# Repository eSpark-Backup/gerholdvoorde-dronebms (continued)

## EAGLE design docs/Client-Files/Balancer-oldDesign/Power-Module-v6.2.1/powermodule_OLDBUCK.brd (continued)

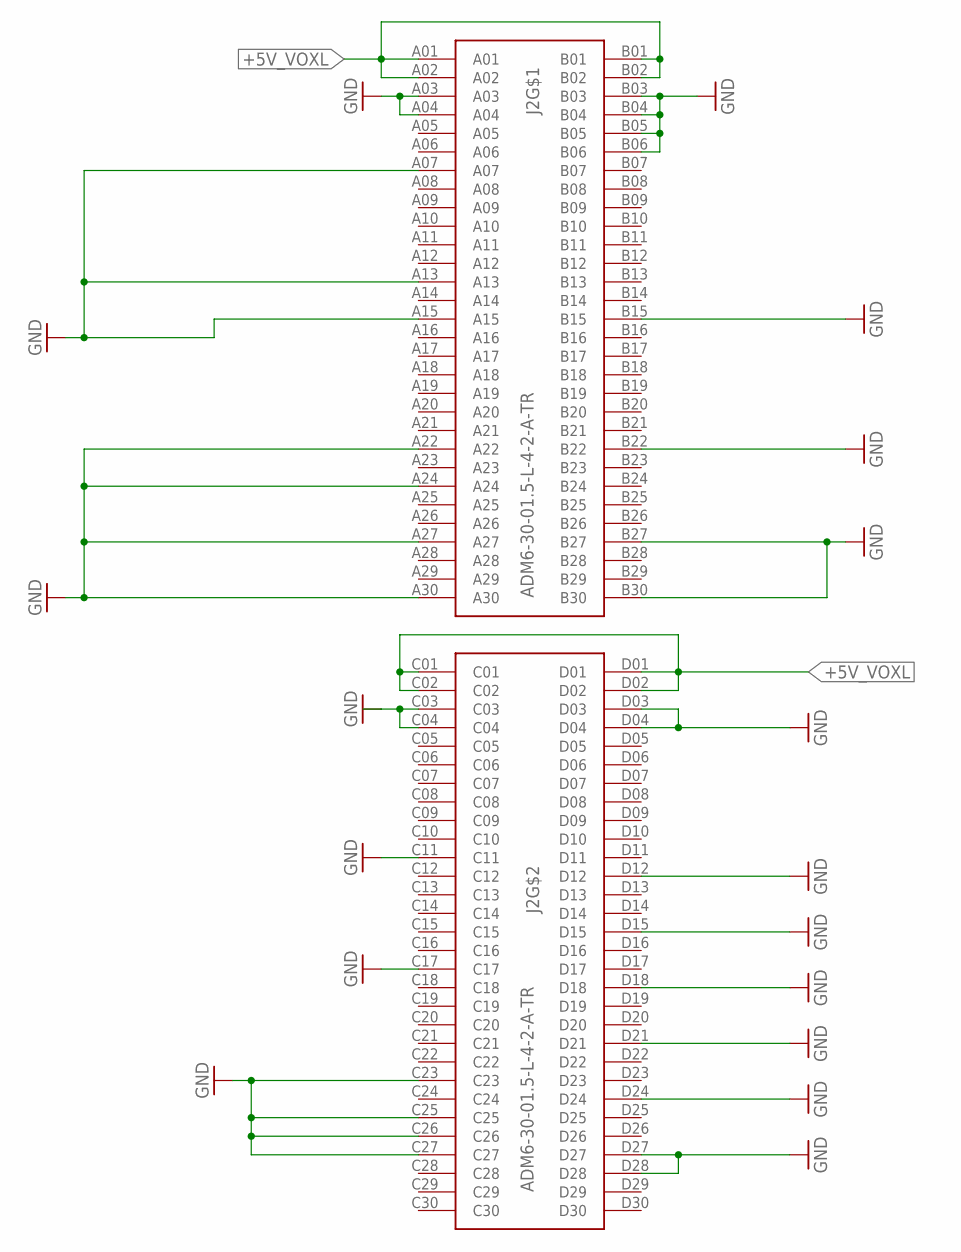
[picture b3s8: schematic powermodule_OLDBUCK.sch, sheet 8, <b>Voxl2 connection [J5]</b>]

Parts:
J2: ADM6-30-01.5-L-4-2-A-TR; SAMTEC_ADM6-30-01.5-L-4-2-A-TR

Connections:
+5V_VOXL: J2.A01, J2.A02, J2.B01, J2.B02, J2.C01, J2.C02, J2.D01, J2.D02; also elsewhere on the board
GND: J2.A03, J2.A04, J2.A07, J2.A13, J2.A15, J2.A22, J2.A24, J2.A27, J2.A30, J2.B03, J2.B04, J2.B05, J2.B06, J2.B15, J2.B22, J2.B27, J2.B30, J2.C03, J2.C04, J2.C11, J2.C17, J2.C23, J2.C25, J2.C26, J2.C27, J2.D03, J2.D04, J2.D12, J2.D15, J2.D18, J2.D21, J2.D24, J2.D27, J2.D28; also elsewhere on the board

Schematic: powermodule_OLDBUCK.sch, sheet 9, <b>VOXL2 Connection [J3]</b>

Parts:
FB: LEDCHIPLED_0805; CHIPLED_0805
J3: QTH-030-01-L-D-ACONN_QTH-030-02-L-D-A-K-FR_S00; CONN_QTH-030-02-L-D-A-K-FR_S00
R11: 1K; R0603
R12: 220?; R0603
U$6: FASTBOOT; EVQ-P7J01P

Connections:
GND: J3.1, J3.10, J3.11, J3.18, J3.21, J3.31, J3.36, J3.44, J3.58, J3.59, R11.2; also elsewhere on the board
GPIO24: R12.2; also elsewhere on the board
unnamed: R11.1, U$6.4
unnamed: FB.C, J3.49, U$6.1
unnamed: FB.A, R12.1
SCL_VOXL: J3.13; also elsewhere on the board
SDA_VOXL: J3.15; also elsewhere on the board
USB-WIFI-DM: J3.12; also elsewhere on the board
USB-WIFI-DP: J3.14; also elsewhere on the board

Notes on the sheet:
Port 9
Note: Deactivate LED when voxl powers on

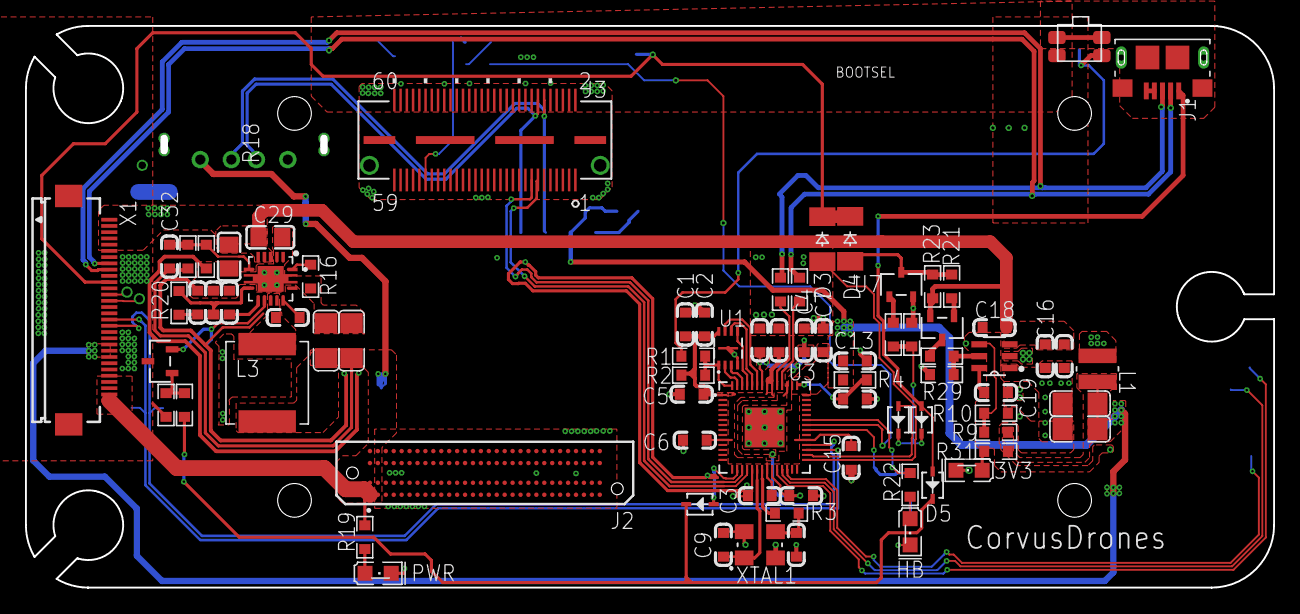
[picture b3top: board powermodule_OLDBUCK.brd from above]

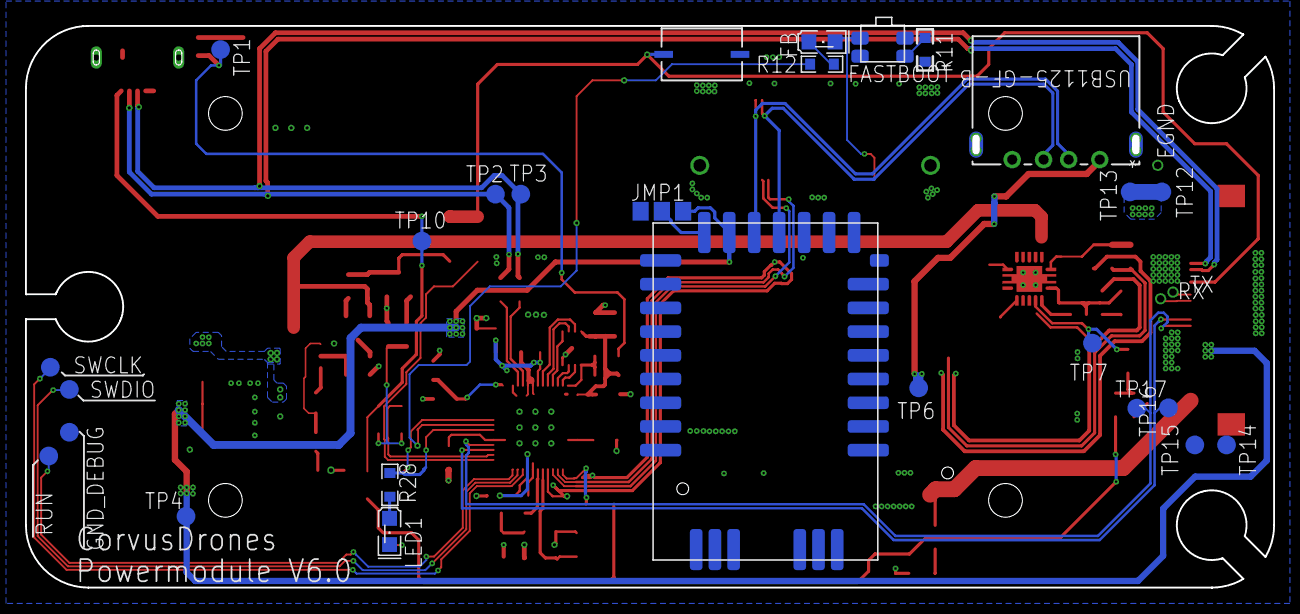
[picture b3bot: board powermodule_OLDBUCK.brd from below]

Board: 2 copper layers, 99.5 x 44.5 mm, 107 parts (30 on the bottom side), 66 nets.

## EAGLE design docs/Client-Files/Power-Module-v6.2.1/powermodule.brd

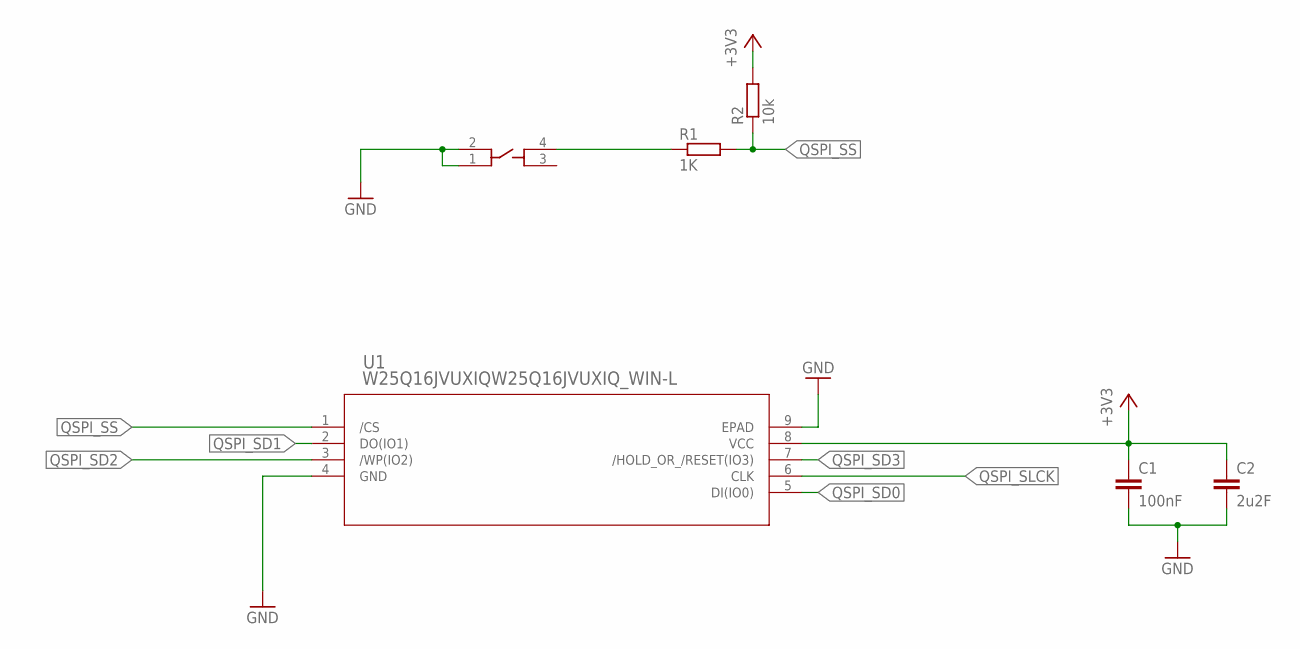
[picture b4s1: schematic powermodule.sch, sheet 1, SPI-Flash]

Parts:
C1: 100nF; C0603
C2: 2u2F; C0603
R1: 1K; R0603
R2: 10k; R0603
SW1: BOOTSEL; EVQ-P7J01P
U1: W25Q16JVUXIQW25Q16JVUXIQ_WIN-L; W25Q16JVUXIQ_WIN-L

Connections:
+3V3: C1.1, C2.1, R2.2, U1.8 (VCC); also elsewhere on the board
GND: C1.2, C2.2, SW1.1, SW1.2, U1.4 (GND), U1.9 (EPAD); also elsewhere on the board
unnamed: R1.1, SW1.4
QSPI_SD0: U1.5 (DI(IO0)); also elsewhere on the board
QSPI_SD1: U1.2 (DO(IO1)); also elsewhere on the board
QSPI_SD2: U1.3 (/WP(IO2)); also elsewhere on the board
QSPI_SD3: U1.7 (/HOLD_OR_/RESET(IO3)); also elsewhere on the board
QSPI_SLCK: U1.6 (CLK); also elsewhere on the board
QSPI_SS: R1.2, R2.1, U1.1 (/CS); also elsewhere on the board

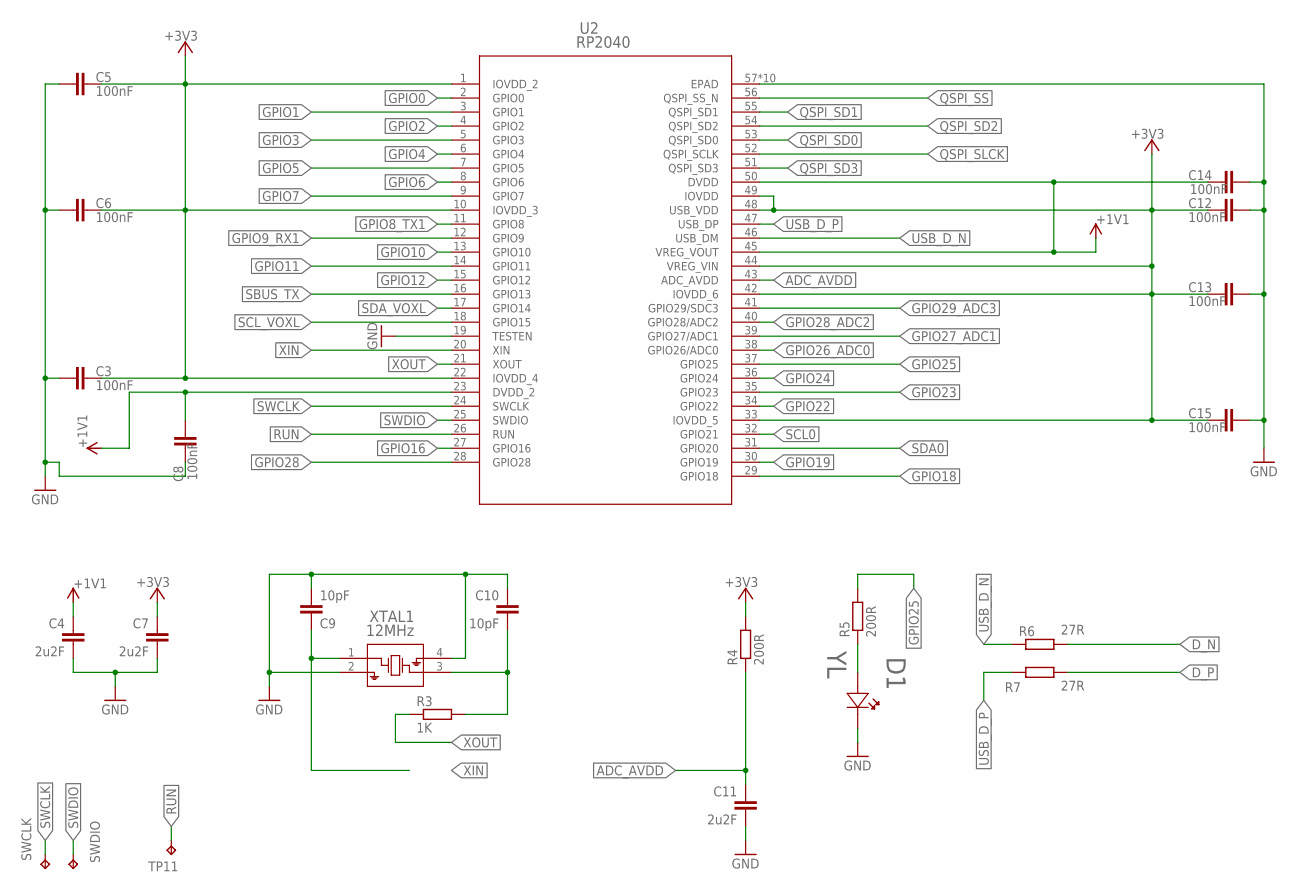
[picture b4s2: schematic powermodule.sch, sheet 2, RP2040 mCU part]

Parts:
C3, C5, C6, C8, C12, C13, C14, C15: 100nF; C0603
C4, C7, C11: 2u2F; C0603
C9, C10: 10pF; C0603
D1: YL; LED_0805
R3: 1K; R0603
R4, R5: 200R; R0603
R6, R7: 27R; R0603
SWCLK: TPTP11R; TP11R
SWDIO: TPTP11R; TP11R
TP11: TPTP11R; TP11R
U2: RP2040; RP2040TR7_RPI-L
XTAL1: 12MHz; SMD3225_3.2X2.5X0.7_MTC-L

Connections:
+1V1: C4.2, C8.1, C14.2, U2.23 (DVDD_2), U2.45 (VREG_VOUT), U2.50 (DVDD)
+3V3: C3.2, C5.1, C6.1, C7.2, C12.1, C13.1, C15.2, R4.2, U2.1 (IOVDD_2), U2.10 (IOVDD_3), U2.22 (IOVDD_4), U2.33 (IOVDD_5), U2.42 (IOVDD_6), U2.44 (VREG_VIN), U2.48 (USB_VDD), U2.49 (IOVDD); also elsewhere on the board
ADC_AVDD: C11.2, R4.1, U2.43 (ADC_AVDD)
D_N: R6.2; also elsewhere on the board
D_P: R7.2; also elsewhere on the board
GND: C3.1, C4.1, C5.2, C6.2, C7.1, C8.2, C9.1, C10.2, C11.1, C12.2, C13.2, C14.1, C15.1, D1.C (1), U2.19 (TESTEN), U2.57 (EPAD), U2.58 (EPAD), U2.59 (EPAD), U2.60 (EPAD), U2.61 (EPAD), U2.62 (EPAD), U2.63 (EPAD), U2.64 (EPAD), U2.65 (EPAD), U2.66 (EPAD), XTAL1.2, XTAL1.4; also elsewhere on the board
GPIO0: U2.2 (GPIO0); also elsewhere on the board
GPIO1: U2.3 (GPIO1); also elsewhere on the board
GPIO2: U2.4 (GPIO2); also elsewhere on the board
GPIO3: U2.5 (GPIO3); also elsewhere on the board
GPIO4: U2.6 (GPIO4); also elsewhere on the board
GPIO5: U2.7 (GPIO5); also elsewhere on the board
GPIO6: U2.8 (GPIO6); also elsewhere on the board
GPIO7: U2.9 (GPIO7); also elsewhere on the board
GPIO8_TX1: U2.11 (GPIO8); also elsewhere on the board
GPIO9_RX1: U2.12 (GPIO9); also elsewhere on the board
GPIO10: U2.13 (GPIO10)
GPIO11: U2.14 (GPIO11)
GPIO12: U2.15 (GPIO12); also elsewhere on the board
GPIO16: U2.27 (GPIO16)
GPIO18: U2.29 (GPIO18)
GPIO19: U2.30 (GPIO19)
GPIO22: U2.34 (GPIO22); also elsewhere on the board
GPIO23: U2.35 (GPIO23); also elsewhere on the board
GPIO24: U2.36 (GPIO24); also elsewhere on the board
GPIO25: R5.2, U2.37 (GPIO25)
GPIO26_ADC0: U2.38 (GPIO26/ADC0); also elsewhere on the board
GPIO27_ADC1: U2.39 (GPIO27/ADC1); also elsewhere on the board
GPIO28: U2.28 (GPIO28); also elsewhere on the board
GPIO28_ADC2: U2.40 (GPIO28/ADC2); also elsewhere on the board
GPIO29_ADC3: U2.41 (GPIO29/SDC3); also elsewhere on the board
unnamed: C10.1, R3.2, XTAL1.3
unnamed: D1.A (2), R5.1
QSPI_SD0: U2.53 (QSPI_SD0); also elsewhere on the board
QSPI_SD1: U2.55 (QSPI_SD1); also elsewhere on the board
QSPI_SD2: U2.54 (QSPI_SD2); also elsewhere on the board
QSPI_SD3: U2.51 (QSPI_SD3); also elsewhere on the board
QSPI_SLCK: U2.52 (QSPI_SCLK); also elsewhere on the board
QSPI_SS: U2.56 (QSPI_SS_N); also elsewhere on the board
RUN: TP11.TP, U2.26 (RUN)
SBUS_TX: U2.16 (GPIO13); also elsewhere on the board
SCL0: U2.32 (GPIO21); also elsewhere on the board
SCL_VOXL: U2.18 (GPIO15); also elsewhere on the board
SDA0: U2.31 (GPIO20); also elsewhere on the board
SDA_VOXL: U2.17 (GPIO14); also elsewhere on the board
SWCLK: SWCLK.TP, U2.24 (SWCLK)
SWDIO: SWDIO.TP, U2.25 (SWDIO)
USB_D_N: R6.1, U2.46 (USB_DM)
USB_D_P: R7.1, U2.47 (USB_DP)
XIN: C9.2, U2.20 (XIN), XTAL1.1
XOUT: R3.1, U2.21 (XOUT)

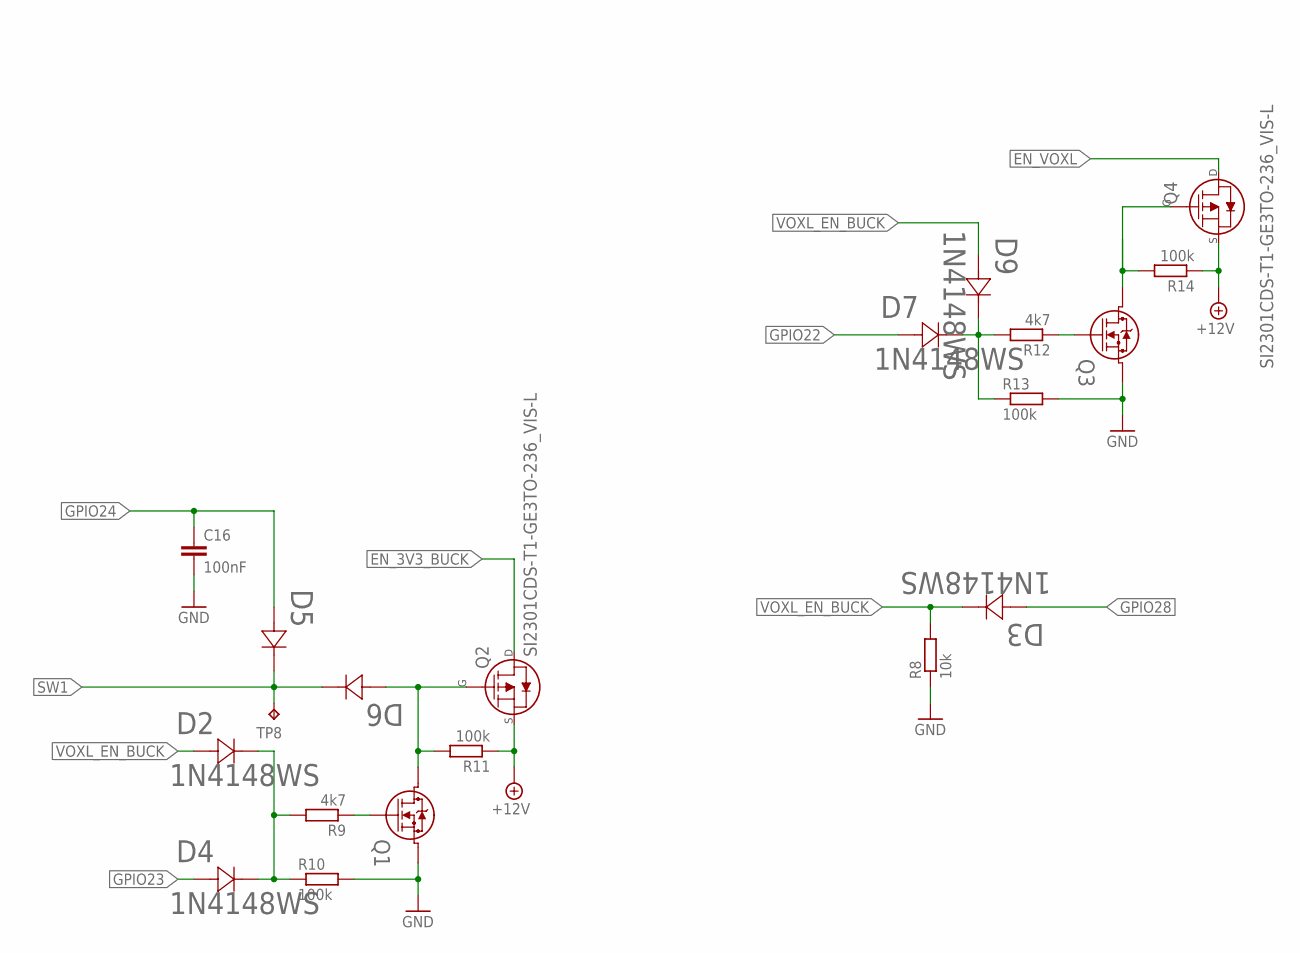
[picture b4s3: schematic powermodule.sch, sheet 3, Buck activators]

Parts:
C16: 100nF; C0603
D2, D3, D4, D7, D9: 1N4148WS; SOD323_NEX-L
D5, D6: MMSD4148T1GSOD-123_ONS-L; SOD-123_ONS-L
Q1, Q3: 2N7002,215TO-236AB_NEX-L; TO-236AB_NEX-L
Q2, Q4: SI2301CDS-T1-GE3TO-236_VIS-L; TO-236_VIS-L
R8: 10k; R0603
R9, R12: 4k7; R0603
R10, R11, R13, R14: 100k; R0603
TP8: TPTP11R; TP11R

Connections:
+12V: Q2.2 (S), Q4.2 (S), R11.1, R14.1; also elsewhere on the board
EN_3V3_BUCK: Q2.3 (D); also elsewhere on the board
EN_VOXL: Q4.3 (D); also elsewhere on the board
GND: C16.2, Q1.2 (3), Q3.2 (3), R8.1, R10.2, R13.2; also elsewhere on the board
GPIO22: D7.2; also elsewhere on the board
GPIO23: D4.2; also elsewhere on the board
GPIO24: C16.1, D5.2; also elsewhere on the board
GPIO28: D3.2; also elsewhere on the board
unnamed: D7.1, D9.1, R12.2, R13.1
unnamed: D6.2, Q1.3 (2), Q2.1 (G), R11.2
unnamed: Q1.1, R9.1
unnamed: Q3.3 (2), Q4.1 (G), R14.2
unnamed: D2.1, D4.1, R9.2, R10.1
unnamed: Q3.1, R12.1
SW1: D5.1, D6.1, TP8.TP; also elsewhere on the board
VOXL_EN_BUCK: D2.2, D3.1, D9.2, R8.2; also elsewhere on the board

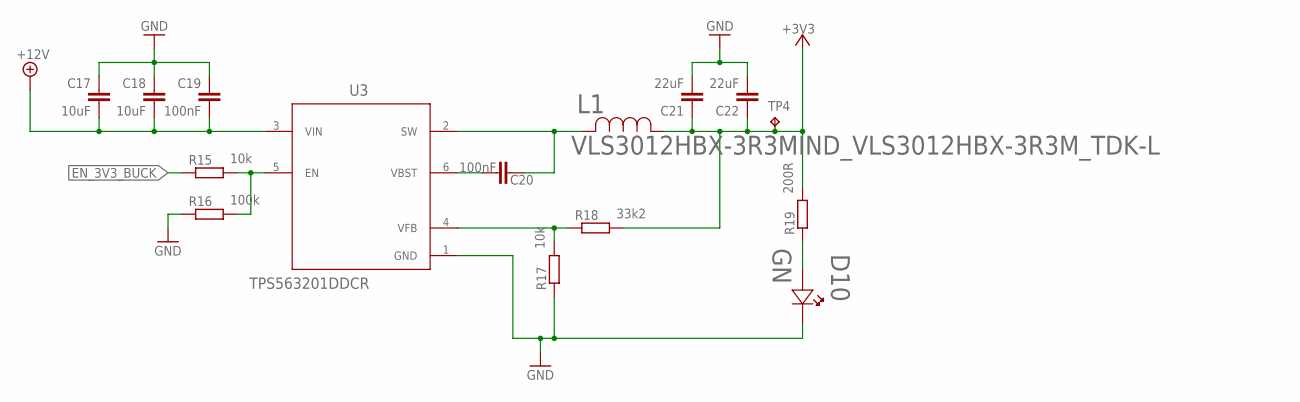
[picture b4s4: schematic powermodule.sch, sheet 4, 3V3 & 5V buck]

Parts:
C17, C18: 10uF; C0603
C19, C20: 100nF; C0603
C21, C22: 22uF; C1206
D10: GN; LED_0805
L1: VLS3012HBX-3R3MIND_VLS3012HBX-3R3M_TDK-L; IND_VLS3012HBX-3R3M_TDK-L
R15, R17: 10k; R0603
R16: 100k; R0603
R18: 33k2; R0603
R19: 200R; R0603
TP4: TPTP11R; TP11R
U3: TPS563201DDCR; DDC0006A_L

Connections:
+3V3: C21.1, C22.1, L1.1, R18.2, R19.2, TP4.TP; also elsewhere on the board
+12V: C17.1, C18.1, C19.1, U3.3 (VIN); also elsewhere on the board
EN_3V3_BUCK: R15.1; also elsewhere on the board
GND: C17.2, C18.2, C19.2, C21.2, C22.2, D10.C (1), R16.1, R17.1, U3.1 (GND); also elsewhere on the board
unnamed: R15.2, R16.2, U3.5 (EN)
unnamed: R17.2, R18.1, U3.4 (VFB)
unnamed: C20.1, U3.6 (VBST)
unnamed: C20.2, L1.2, U3.2 (SW)
unnamed: D10.A (2), R19.1

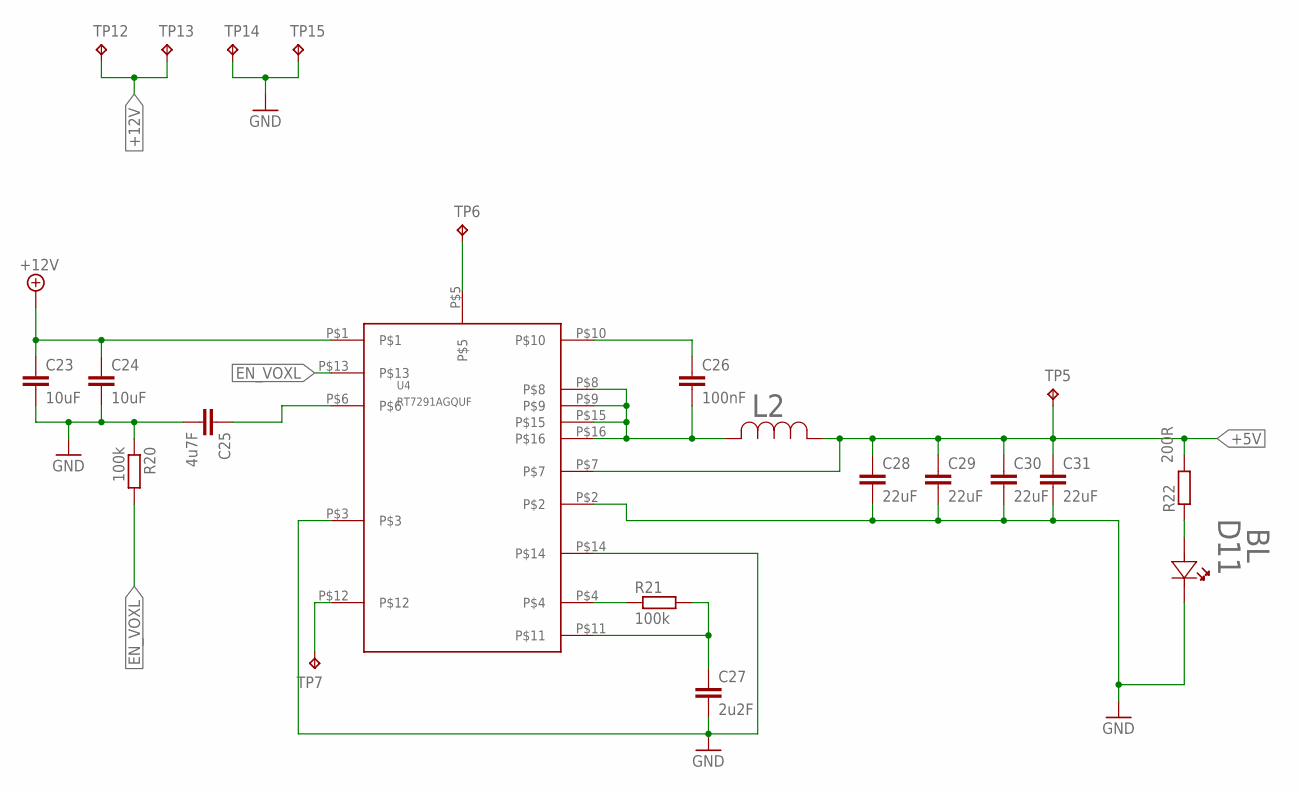
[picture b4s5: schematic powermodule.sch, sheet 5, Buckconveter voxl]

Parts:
C23, C24: 10uF; C0805
C25: 4u7F; C0603
C26: 100nF; C0603
C27: 2u2F; C0603
C28, C29, C30, C31: 22uF; C1206
D11: BL; LED_0805
L2: HA72L-06301R5LFTR
R20, R21: 100k; R0603
R22: 200R; R0603
TP5, TP6, TP7, TP12, TP13, TP14, TP15: TPTP11R; TP11R
U4: RT7291AGQUF

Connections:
+5V: C28.1, C29.1, C30.1, C31.1, L2.P$1 (1), R22.2, TP5.TP, U4.P$7; also elsewhere on the board
+12V: C23.1, C24.1, TP12.TP, TP13.TP, U4.P$1; also elsewhere on the board
EN_VOXL: R20.2, U4.P$13; also elsewhere on the board
GND: C23.2, C24.2, C25.2, C27.2, C28.2, C29.2, C30.2, C31.2, D11.C (1), R20.1, TP14.TP, TP15.TP, U4.P$2, U4.P$3, U4.P$14; also elsewhere on the board
unnamed: C26.2, L2.P$2 (2), U4.P$8, U4.P$9, U4.P$15, U4.P$16
unnamed: C25.1, U4.P$6
unnamed: C27.1, R21.2, U4.P$11
unnamed: TP7.TP, U4.P$12
unnamed: R21.1, U4.P$4
unnamed: D11.A (2), R22.1
unnamed: TP6.TP, U4.P$5
unnamed: C26.1, U4.P$10

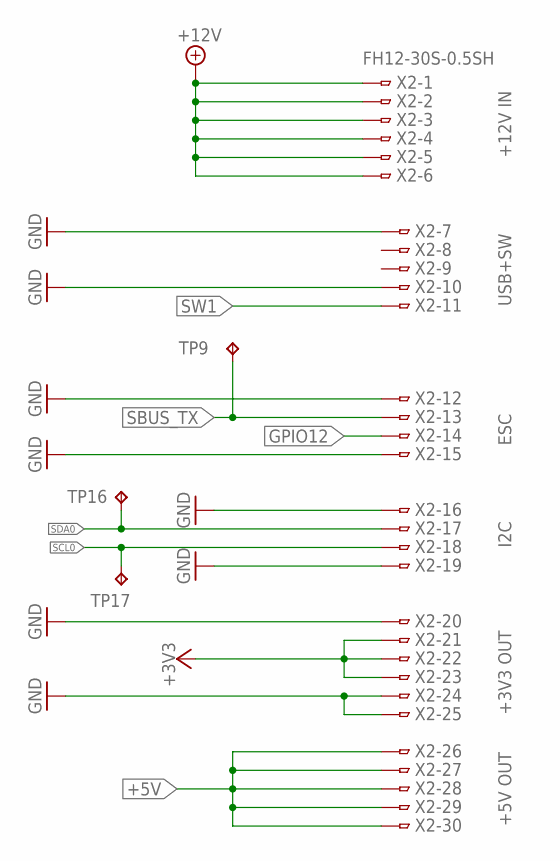
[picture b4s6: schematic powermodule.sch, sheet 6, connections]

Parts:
TP9, TP16, TP17: TPTP11R; TP11R
X2: FH12-30S-0.5SH

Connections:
+3V3: X2.21, X2.22, X2.23; also elsewhere on the board
+5V: X2.26, X2.27, X2.28, X2.29, X2.30; also elsewhere on the board
+12V: X2.1, X2.2, X2.3, X2.4, X2.5, X2.6; also elsewhere on the board
GND: X2.7, X2.10, X2.12, X2.15, X2.16, X2.19, X2.20, X2.24, X2.25; also elsewhere on the board
GPIO12: X2.14; also elsewhere on the board
SBUS_TX: TP9.TP, X2.13; also elsewhere on the board
SCL0: TP17.TP, X2.18; also elsewhere on the board
SDA0: TP16.TP, X2.17; also elsewhere on the board
SW1: X2.11; also elsewhere on the board

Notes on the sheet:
+5V OUT
+3V3 OUT
I2C
ESC
USB+SW
+12V IN

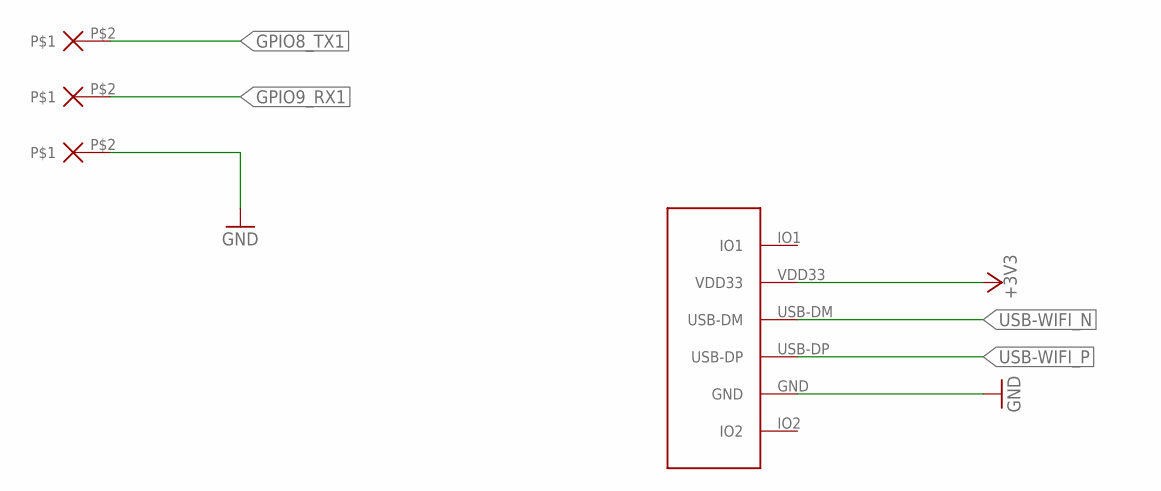
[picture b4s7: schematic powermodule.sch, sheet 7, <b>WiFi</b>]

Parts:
GND_SER: TH-0.75/0.6
W1: WIFI-RTL8188EUS
X3, X4: TH-0.75/0.6

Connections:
+3V3: W1.VDD33; also elsewhere on the board
GND: GND_SER.P$2, W1.GND; also elsewhere on the board
GPIO8_TX1: X3.P$2; also elsewhere on the board
GPIO9_RX1: X4.P$2; also elsewhere on the board
USB-WIFI_N: W1.USB-DM; also elsewhere on the board
USB-WIFI_P: W1.USB-DP; also elsewhere on the board

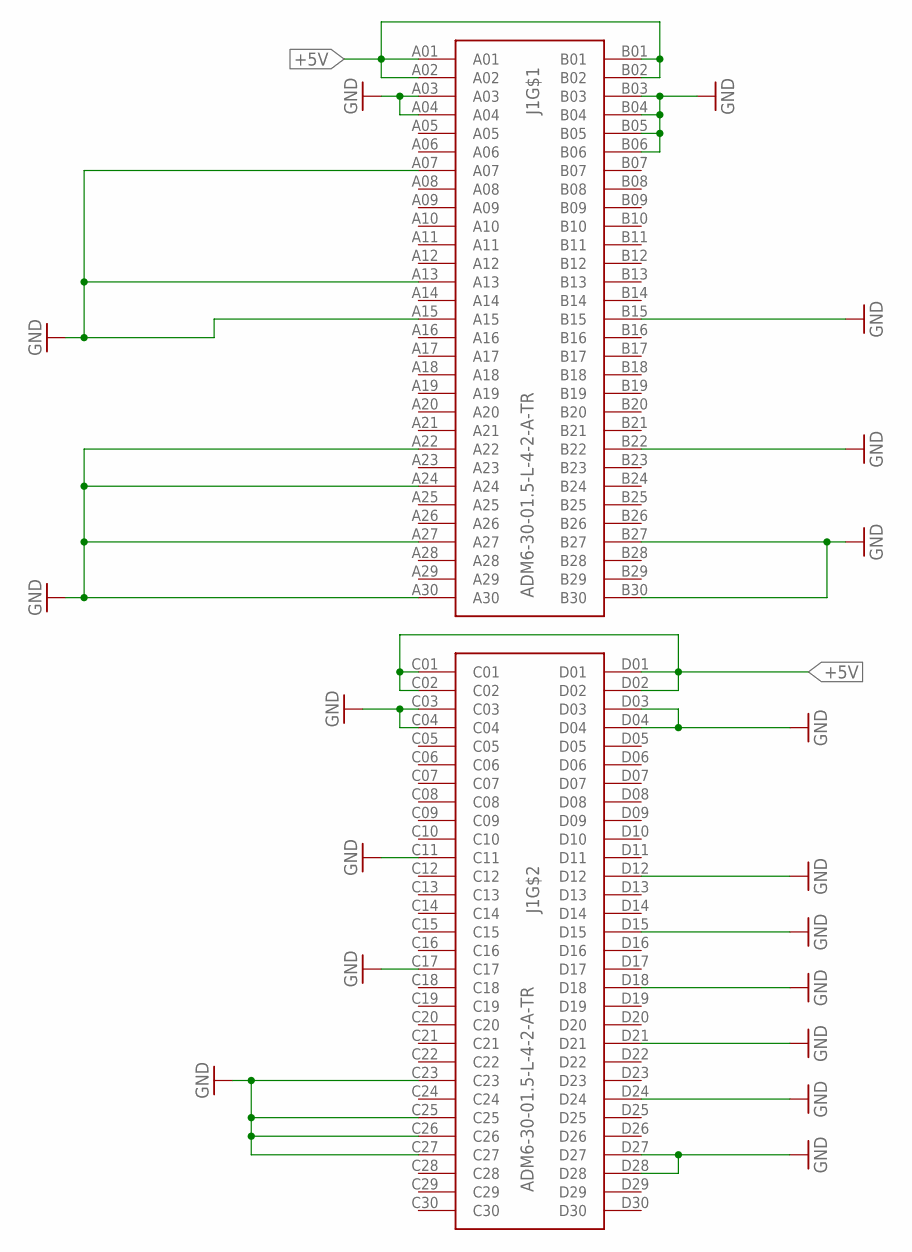
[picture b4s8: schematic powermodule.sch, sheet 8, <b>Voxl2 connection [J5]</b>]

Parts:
J1: ADM6-30-01.5-L-4-2-A-TR; SAMTEC_ADM6-30-01.5-L-4-2-A-TR

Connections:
+5V: J1.A01, J1.A02, J1.B01, J1.B02, J1.C01, J1.C02, J1.D01, J1.D02; also elsewhere on the board
GND: J1.A03, J1.A04, J1.A07, J1.A13, J1.A15, J1.A22, J1.A24, J1.A27, J1.A30, J1.B03, J1.B04, J1.B05, J1.B06, J1.B15, J1.B22, J1.B27, J1.B30, J1.C03, J1.C04, J1.C11, J1.C17, J1.C23, J1.C25, J1.C26, J1.C27, J1.D03, J1.D04, J1.D12, J1.D15, J1.D18, J1.D21, J1.D24, J1.D27, J1.D28; also elsewhere on the board

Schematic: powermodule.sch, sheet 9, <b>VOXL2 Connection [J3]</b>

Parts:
D12: YL; LED_0805
J2: QTH-030-01-L-D-ACONN_QTH-030-02-L-D-A-K-FR_S00; CONN_QTH-030-02-L-D-A-K-FR_S00
R23: 200R; R0603
R24: 1K; R0603
SW2: FASTBOOT; EVQ-P7J01P

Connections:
BOOTSEL_MCU: J2.17
GND: J2.1, J2.10, J2.11, J2.18, J2.21, J2.31, J2.36, J2.44, J2.58, J2.59, R24.2; also elsewhere on the board
GPIO7: R23.2; also elsewhere on the board
unnamed: R24.1, SW2.4
unnamed: D12.C (1), J2.49, SW2.1
unnamed: D12.A (2), R23.1
RESET_MCU: J2.9
RESET_USB_HUB: J2.19
SCL_VOXL: J2.13; also elsewhere on the board
SDA_VOXL: J2.15; also elsewhere on the board
VOXL_EN_BUCK: J2.7; also elsewhere on the board
VOXL_USB_N: J2.12; also elsewhere on the board
VOXL_USB_P: J2.14; also elsewhere on the board

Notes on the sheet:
Port 9
Note: Deactivate LED when voxl powers on

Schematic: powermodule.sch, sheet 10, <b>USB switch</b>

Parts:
C32, C34: 1uF; C0603
C33: 100nF; C0603
C35, C36: 10pF; C0603
R25, R26, R28: 50k; R0603
R27: 12k; R0603
TP19: TPTP11R; TP11R
U5: USB2422/MJ_SQFN-4X4; SQFN24_4X4
XTAL2: 24MHz; SMD3225_3.2X2.5X0.7_MTC-L

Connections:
+3V3: C32.1, C33.1, R25.2, U5.1 (VDD33_2), U5.9 (VDD33_3), U5.16 (VBUS_DET), U5.18 (VDD33); also elsewhere on the board
D_N: U5.4 (USBDP_DN1/PRT_DIS_M2); also elsewhere on the board
D_P: U5.5 (USBDM_DN2/PRT_DIS_P2); also elsewhere on the board
GND: C32.2, C33.2, C34.2, C35.2, C36.1, R26.2, R27.2, R28.2, U5.25 (EPAD), XTAL2.2, XTAL2.4; also elsewhere on the board
HUB_RESET: TP19.TP, U5.15 (RESET_N)
unnamed: R27.1, U5.24 (RBIAS)
unnamed: C36.2, U5.21 (XTALOUT!(CLKIN_EN)), XTAL2.3
unnamed: C35.1, U5.22 (XTALIN/CLKIN), XTAL2.1
unnamed: R26.1, U5.14 (SMBCLK/CFG_SEL0)
unnamed: R25.1, U5.13 (SMBDATA/NON_REM1)
unnamed: R28.1, U5.17 (SUSP_IND/LOCAL_PWR!NON_REM0)
unnamed: C34.1, U5.10 (CRFILT)
PRTPWR2: U5.11 (PRTPWR2)
USB-WIFI_N: U5.2 (USBDP_DN1/PRT_DIS_M1); also elsewhere on the board
USB-WIFI_P: U5.3 (USBDP_DN1/PRT_DIS_P1); also elsewhere on the board
VOXL_USB_N: U5.19 (USBDM_UP); also elsewhere on the board
VOXL_USB_P: U5.20 (USBDP_UP); also elsewhere on the board

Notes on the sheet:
Config CGF 1 R17 = PULLDOWN R35 = PULLUP CFG 2 R20 no place = PULLDOWN R20 place = PULLUP

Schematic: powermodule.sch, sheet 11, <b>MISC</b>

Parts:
H1, H2, H3, H4: SMT_SPACER_5MMX2.5M
XP1, XP2, XP3, XP4, XP5, XP6, XP7, XP8, XP9, XP10, XP11: SMT-PAD_R1-5MM

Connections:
GND: H1.P$1, H2.P$1, H3.P$1, H4.P$1; also elsewhere on the board
GPIO0: XP1.P$1; also elsewhere on the board
GPIO1: XP11.P$1; also elsewhere on the board
GPIO2: XP2.P$1; also elsewhere on the board
GPIO3: XP3.P$1; also elsewhere on the board
GPIO4: XP4.P$1; also elsewhere on the board
GPIO5: XP5.P$1; also elsewhere on the board
GPIO6: XP10.P$1; also elsewhere on the board
GPIO26_ADC0: XP6.P$1; also elsewhere on the board
GPIO27_ADC1: XP7.P$1; also elsewhere on the board
GPIO28_ADC2: XP8.P$1; also elsewhere on the board
GPIO29_ADC3: XP9.P$1; also elsewhere on the board

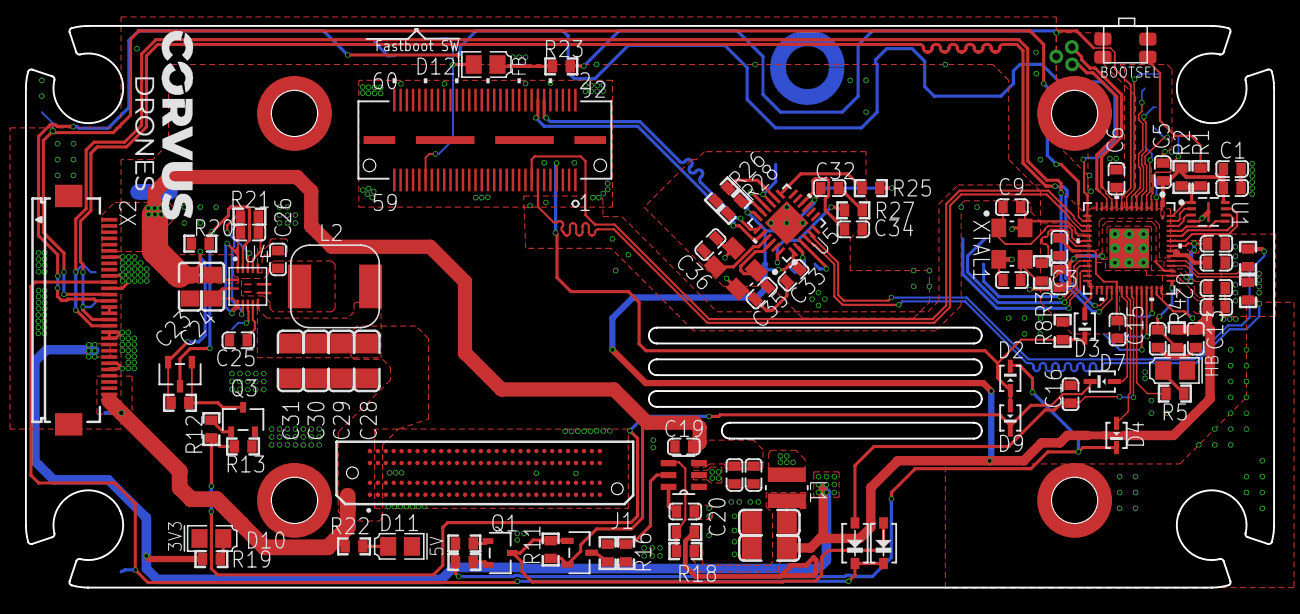
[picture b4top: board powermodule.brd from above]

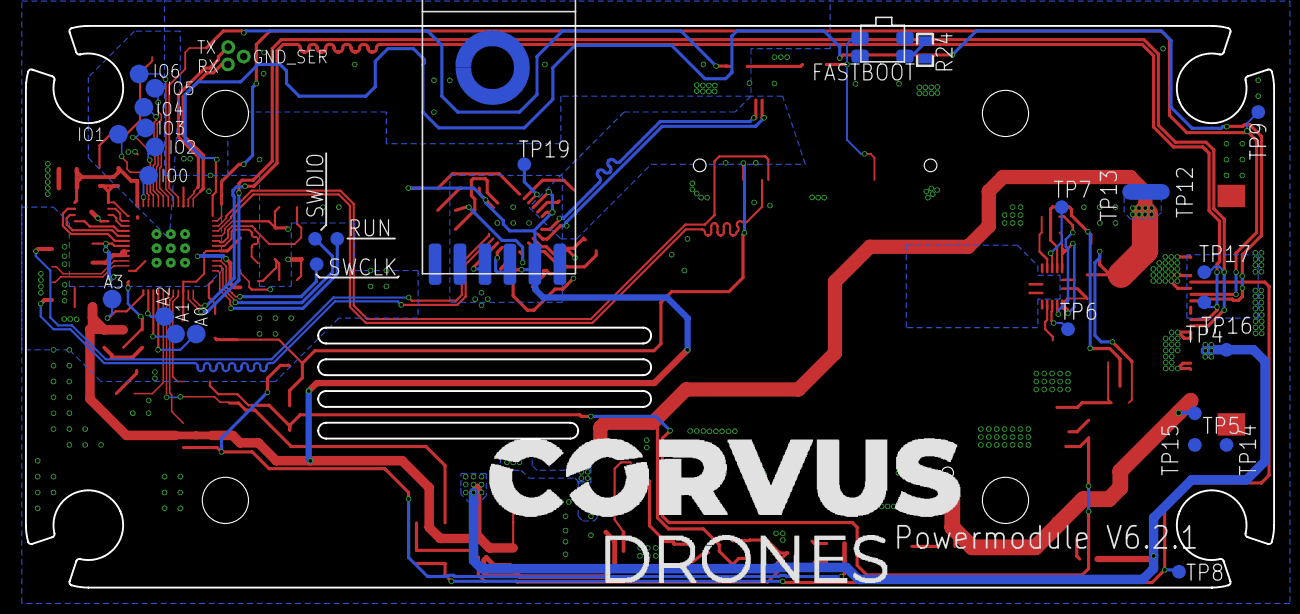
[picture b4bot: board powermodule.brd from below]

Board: 2 copper layers, 100.0 x 45.0 mm, 128 parts (33 on the bottom side), 87 nets.

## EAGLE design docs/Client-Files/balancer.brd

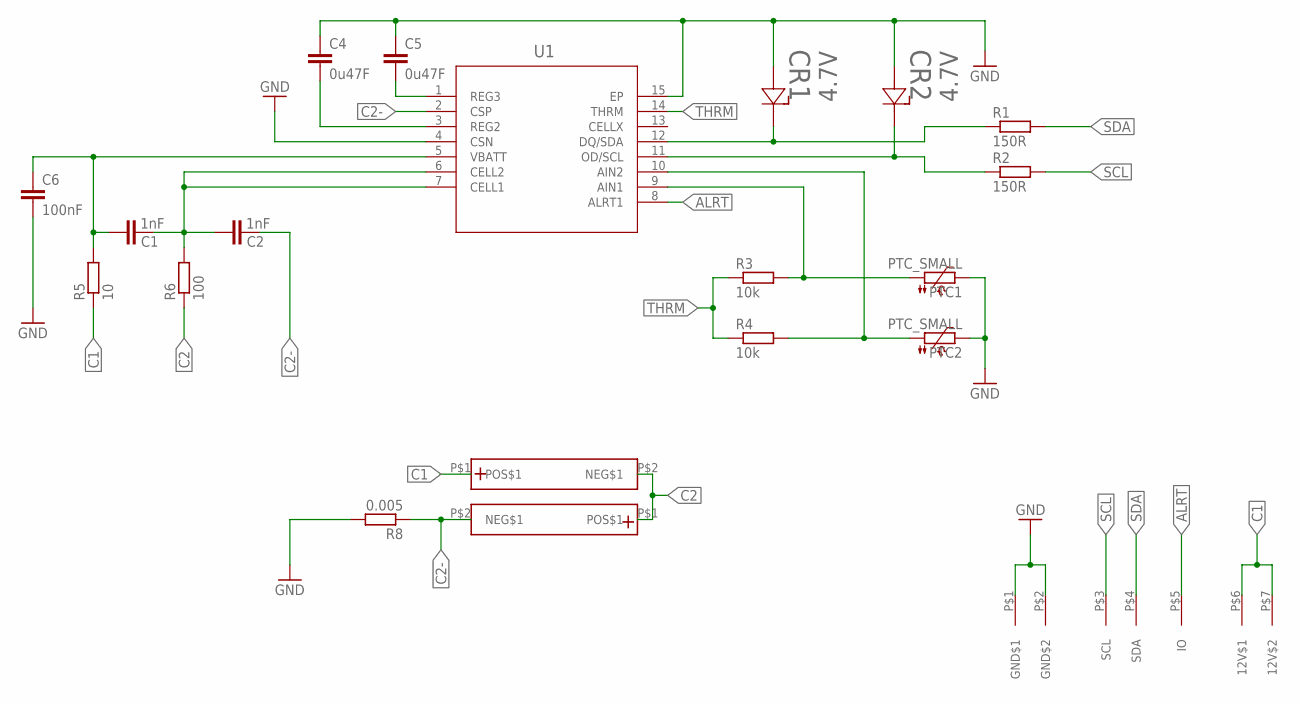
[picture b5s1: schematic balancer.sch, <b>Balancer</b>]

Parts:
C1, C2: 1nF; C0603
C4, C5: 0u47F; C0603
C6: 100nF; C0603
CR1, CR2: 4u7 ZEN; SOD323_NEX-L
PTC1, PTC2: PTC_SMALL; P660
R1, R2: 150R; R0603
R3, R4: 10k; R0603
R5: 10; R1206
R6: 100; R1206
R8: 0.005; R4527
U1: MAX17205G+; TDFN-15
U$1, U$2: BATT_CELL
U$4: BATT_CON_THT

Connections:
ALRT: U1.8 (ALRT1), U$4.P$5 (IO)
C1: R5.1, U$1.P$1 (POS$1), U$4.P$6 (12V$1), U$4.P$7 (12V$2)
C2: R6.1, U$1.P$2 (NEG$1), U$2.P$1 (POS$1)
C2-: C2.1, R8.1, U1.2 (CSP), U$2.P$2 (NEG$1)
GND: C4.1, C5.1, C6.2, CR1.2, CR2.2, PTC1.2, PTC2.2, R8.2, U1.4 (CSN), U1.15 (EP), U$4.P$1 (GND$1), U$4.P$2 (GND$2)
unnamed: CR1.1, R1.1, U1.12 (DQ/SDA)
unnamed: CR2.1, R2.1, U1.11 (OD/SCL)
unnamed: PTC2.1, R4.2, U1.10 (AIN2)
unnamed: PTC1.1, R3.2, U1.9 (AIN1)
unnamed: C5.2, U1.1 (REG3)
unnamed: C4.2, U1.3 (REG2)
unnamed: C1.1, C2.2, R6.2, U1.6 (CELL2), U1.7 (CELL1)
unnamed: C1.2, C6.1, R5.2, U1.5 (VBATT)
SCL: R2.2, U$4.P$3 (SCL)
SDA: R1.2, U$4.P$4 (SDA)
THRM: R3.1, R4.1, U1.14 (THRM)

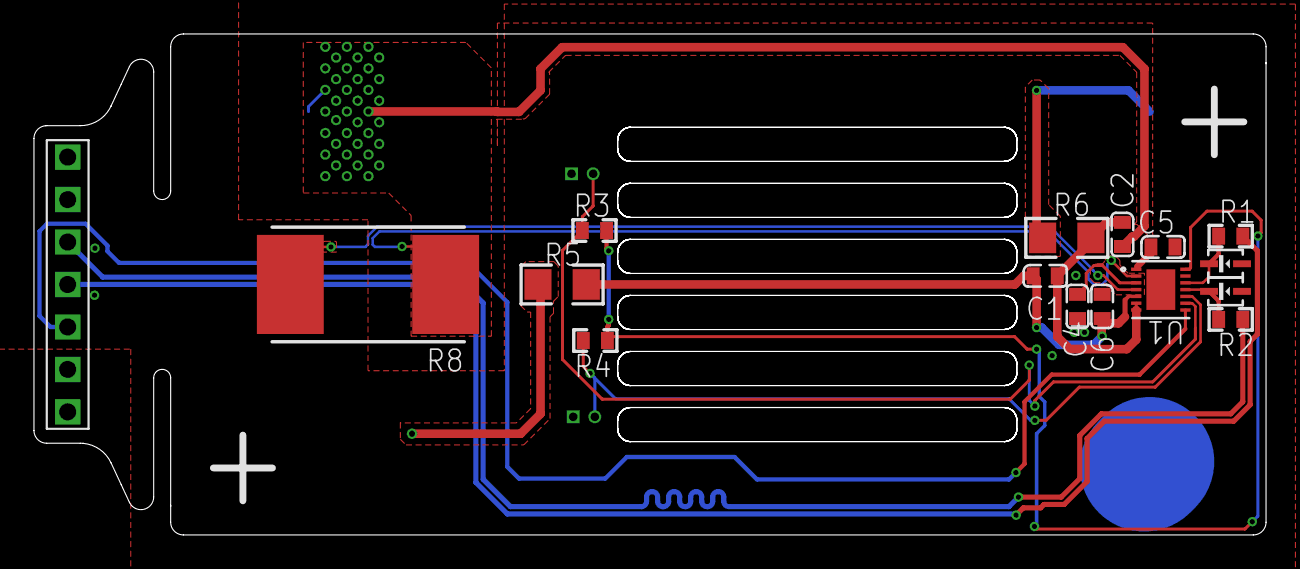
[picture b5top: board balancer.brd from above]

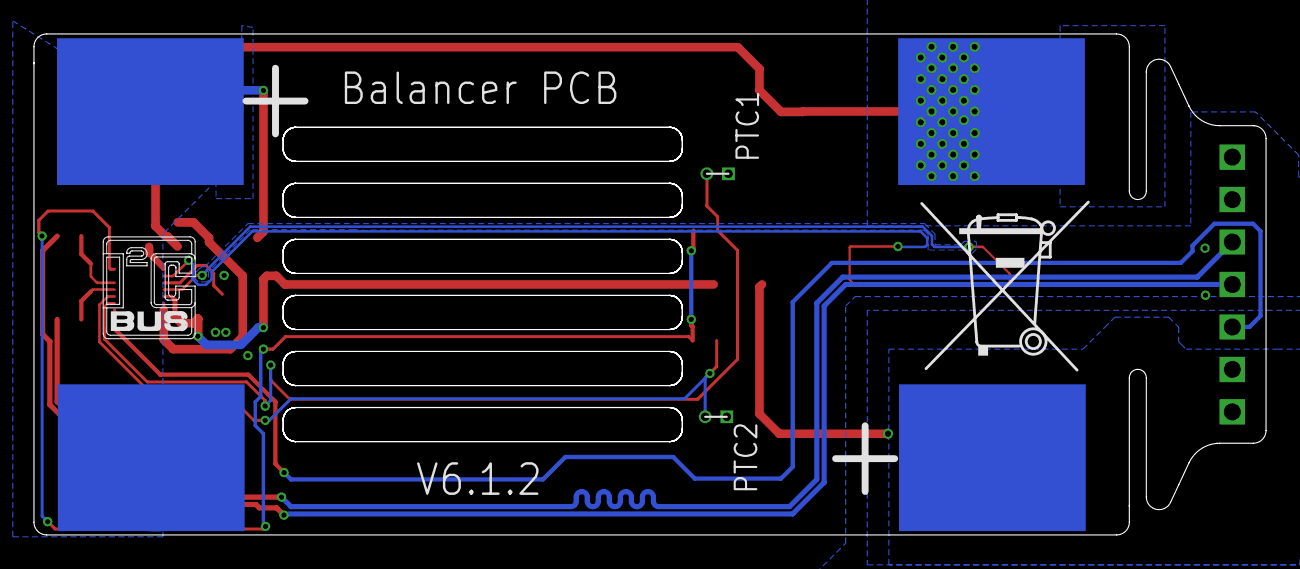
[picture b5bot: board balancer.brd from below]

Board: 2 copper layers, 72.5 x 29.5 mm, 22 parts (4 on the bottom side), 16 nets.

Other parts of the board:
U$5: I2C
U$6: MUELLTONNE_10.00
